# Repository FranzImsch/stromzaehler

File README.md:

## Hardware
Features:
- IR interface for a [smart (DE)](https://youtu.be/aqHauk3bNFA) electricity meter,
- binary input for a gas meter (impulse counter),
- high efficiency buck converter for the USB power supply.

The interface is mounted to the electricity meter using a ring magnet (27 x 5 x 16 mm). The magnet is glued into the 3D-printed [plastic part](https://github.com/FranzImsch/stromzaehler/blob/main/plastic_mount.step) as shown in the picture below.

A [threaded insert (M2)](https://www.digikey.de/en/products/detail/tri-star-industries-inc/M20X157C/13535373) is melted into the plastic piece so that the PCB can be mounted using an M2x5 screw.

Detailed overview: https://a360.co/3Tq192N

Some electricity meters send data without 'request' and therefore the IR-LED along with its circuitry can be omitted in those cases. The [Volkszähler (DE)](https://wiki.volkszaehler.org/hardware/channels/meters) site is pretty useful to find information about different meters.

## Software
For Tasmota to use the SML feature, the following must be added to the ```user_config_override.h```-File (as per [documentation](https://tasmota.github.io/docs/Smart-Meter-Interface/)):

```
#ifndef USE_SCRIPT
#define USE_SCRIPT
#endif
#ifndef USE_SML_M
#define USE_SML_M
#endif
#ifdef USE_RULES
#undef USE_RULES
#endif
```
The software is compiled using the 8M tasmota32 preset. Flashed using [this](https://github.com/FranzImsch/CP2104-M8) serial adapter.

As soon as the device is connected to WiFi, the script for the electricity meter can be entered into the console (as per [documentation](https://tasmota.github.io/docs/Smart-Meter-Interface/#iskra-mt-681-sml)). The RX (25) and TX (26) GPIOs have to be adjusted. The script might need to be adjusted for the very meter that is used. For that, [this](https://tasmota-sml-parser.azurewebsites.net/) tool was tremendously helpful.

The **gas meter** is read with a reed contact. IO27 is set as a counter in Tasmota. What 1 Tick corresponds to in terms of gas is usually written somewhere on the meter. The counter is debounced using the [```CounterDebounce 250```](https://tasmota.github.io/docs/Commands/#sensors) command (which corresponds to 250 ms debounce time).

Also, the TelePeriod was set to 10 seconds (the fastest) as per [documentation](https://tasmota.github.io/docs/Commands/#mqtt).

## Links
- [3D model](https://a360.co/3Tq192N)  
- [Schematic](https://franz.science/stromzaehler/KiCad-Files/Schematic.pdf)  
- [iBom](https://franz.science/stromzaehler/ibom/)  
- [Tasmota](https://github.com/arendst/tasmota)

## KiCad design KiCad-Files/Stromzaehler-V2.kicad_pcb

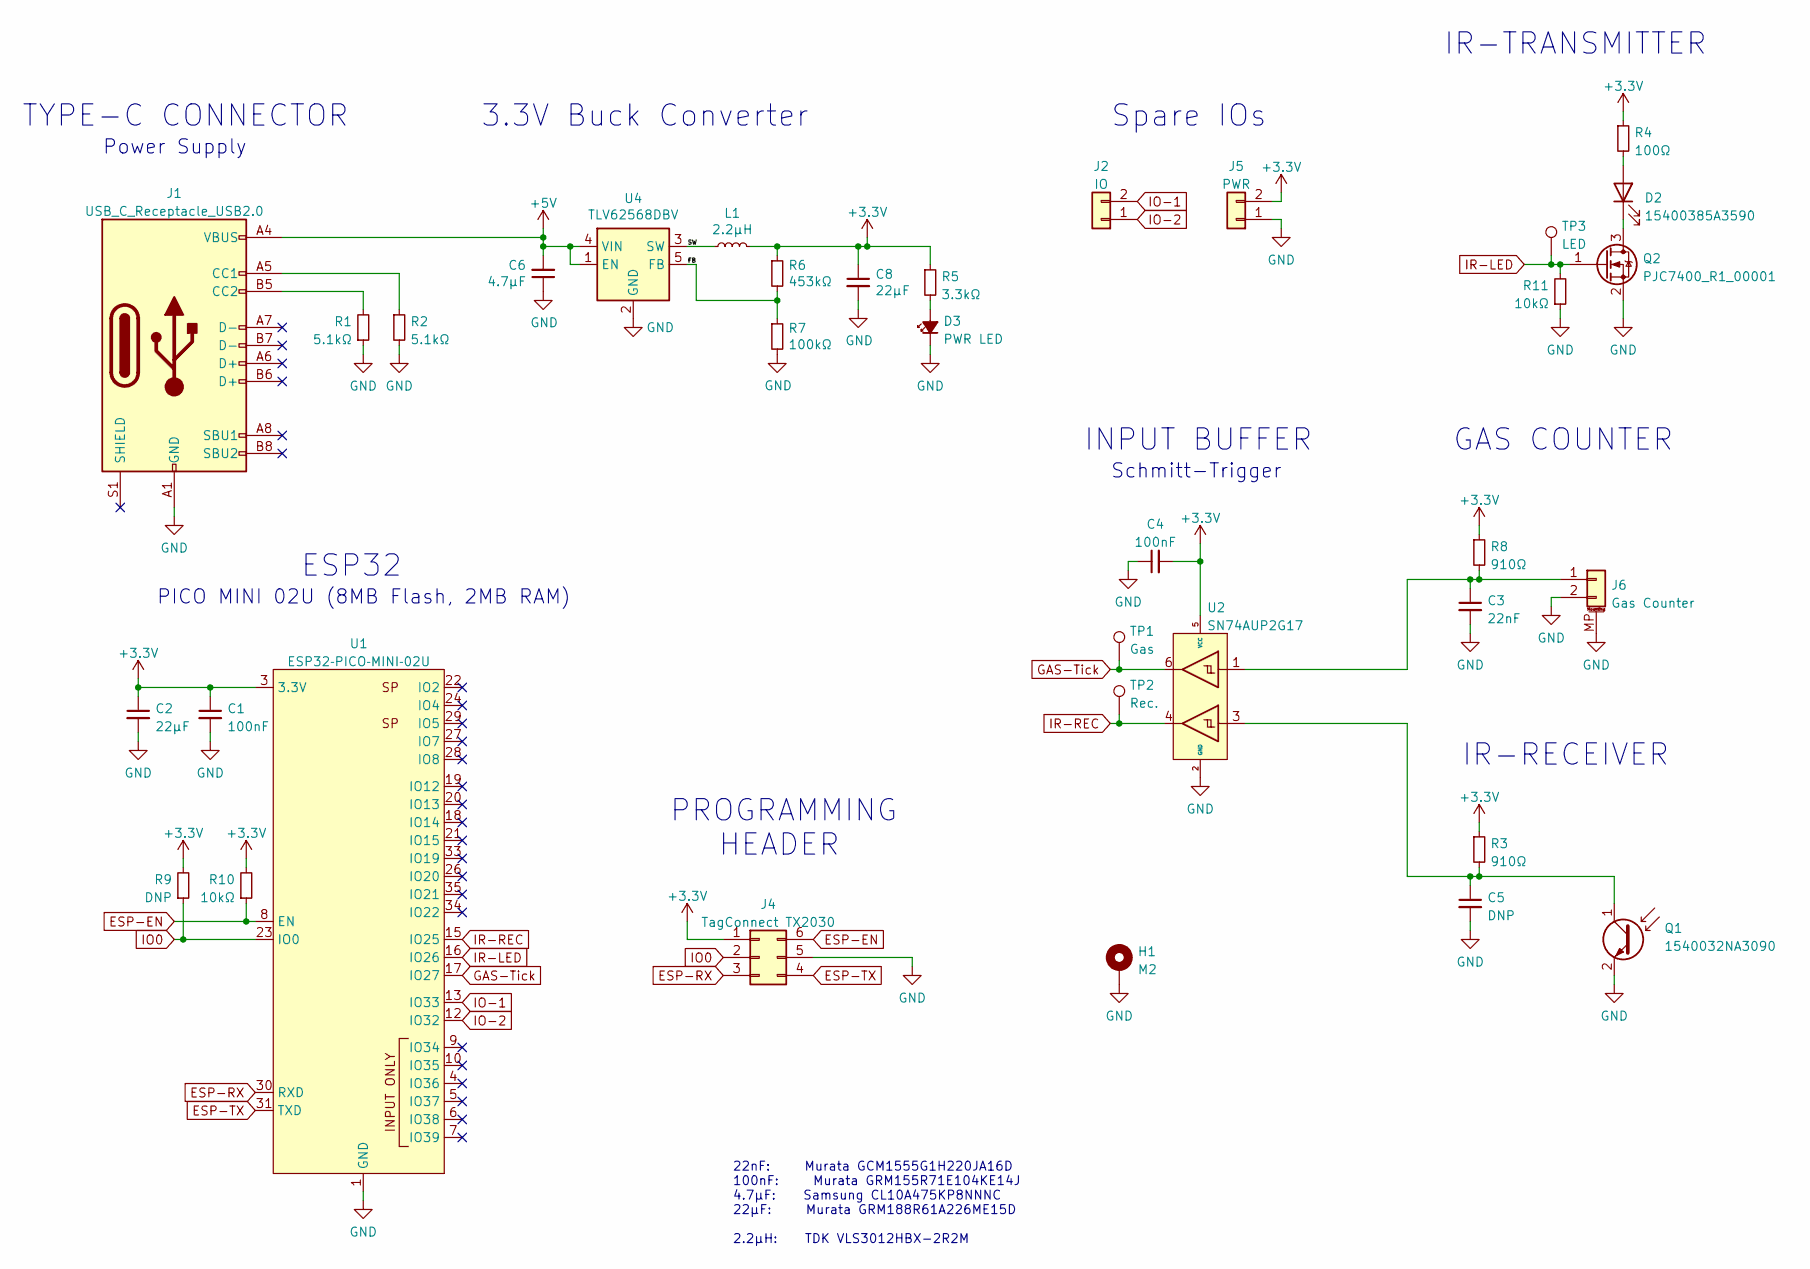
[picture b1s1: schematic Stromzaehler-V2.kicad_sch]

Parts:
C1, C4: 100nF; C_0402_1005Metric_NoSilk
C2, C8: 22µF; C_0603_1608Metric_NoSilk
C3: 22nF; C_0402_1005Metric_NoSilk
C5: DNP; C_0402_1005Metric_NoSilk_DNP
C6: 4.7µF; C_0603_1608Metric_NoSilk
D2: 15400385A3590; LED_D3.0mm_IRBlack_NoSillk
D3: PWR LED; LED_0603_1608Metric_SmallSilk
H1: M2; MountingHole_2.2mm_M2_Pad_Via_NoSilk
J1: USB_C_Receptacle_USB2.0; USB_C_Receptacle_C313131_TYPE-C-31-M-12
J2: IO; PinHeader_1x02_P2.54mm_Vertical_NoSilk
J4: TagConnect TX2030; Tag-Connect_TC2030-IDC-NL_2x03_P1.27mm_Vertical_NoSilk
J5: PWR; PinHeader_1x02_P2.54mm_Vertical_NoSilk
J6: Gas Counter; JST_SH_SM02B-SRSS-TB_1x02-1MP_P1.00mm_Horizontal_NoSilk
L1: 2.2µH; L_Wuerth_MAPI-3012_NoSilk
Q1: 1540032NA3090; LED_D3.0mm_IRBlack_NoSillk
Q2: PJC7400_R1_00001; SOT-323_SC-70_NoSilk
R1, R2: 5.1kΩ; R_0402_1005Metric_NoSilk
R3, R8: 910Ω; R_0402_1005Metric_NoSilk
R4: 100Ω; R_0603_1608Metric_NoSilk
R5: 3.3kΩ; R_0402_1005Metric_NoSilk
R6: 453kΩ; R_0603_1608Metric_NoSilk
R7: 100kΩ; R_0603_1608Metric_NoSilk
R9: DNP; R_0402_1005Metric_NoSilk_DNP
R10, R11: 10kΩ; R_0402_1005Metric_NoSilk
TP1: Gas; TestPoint_Pad_D1.0mm_NoSIlk
TP2: Rec.; TestPoint_Pad_D1.0mm_NoSIlk
TP3: LED; TestPoint_Pad_D1.0mm_NoSIlk
U1: ESP32­PICO­MINI­02U; ESP32-PICO-MINI-02U
U2: SN74AUP2G17; SOT-363_SC-70-6_NoSilk
U4: TLV62568DBV; SOT-23-5_NoSilk

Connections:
+3.3V: C1.1, C2.1, C4.2, C8.1, J4.1, J5.2, L1.2, R3.1, R4.1, R5.1, R6.1, R8.1, R9.2, R10.2, U1.3 (3.3V), U2.5 (VCC)
+5V: C6.2, J1.A4 (VBUS), J1.A9 (VBUS), J1.B4 (VBUS), J1.B9 (VBUS), U4.1 (EN), U4.4 (VIN)
/FB: R6.2, R7.1, U4.5 (FB)
/SW: L1.1, U4.3 (SW)
ESP-EN: J4.6, R10.1, U1.8 (EN)
ESP-RX: J4.3, U1.30 (RXD)
ESP-TX: J4.4, U1.31 (TXD)
GAS-Tick: TP1.1, U1.17 (IO27), U2.6
GND: C1.2, C2.2, C3.2, C4.1, C5.2, C6.1, C8.2, D3.1 (K), H1.1, J1.A1 (GND), J1.A12 (GND), J1.B1 (GND), J1.B12 (GND), J4.5, J5.1, J6.2, J6.MP (MountPin), Q1.2 (E), Q2.2 (S), R1.1, R2.2, R7.2, R11.1, U1.1 (GND), U1.2 (GND), U1.11 (GND), U1.14 (GND), U1.49 (GND), U2.2 (GND), U4.2 (GND)
IO0: J4.2, R9.1, U1.23 (IO0)
IO-1: J2.2, U1.13 (IO33)
IO-2: J2.1, U1.12 (IO32)
IR-LED: Q2.1 (G), R11.2, TP3.1, U1.16 (IO26)
IR-REC: TP2.1, U1.15 (IO25), U2.4
unnamed: C3.1, J6.1, R8.2, U2.1
unnamed: C5.1, Q1.1 (C), R3.2, U2.3
unnamed: D2.1 (K), Q2.3 (D)
unnamed: D2.2 (A), R4.2
unnamed: D3.2 (A), R5.2
unnamed: J1.A5 (CC1), R2.1
unnamed: J1.B5 (CC2), R1.2

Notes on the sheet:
INPUT BUFFER
Spare IOs
GAS COUNTER
22nF: Murata GCM1555G1H220JA16D 100nF: Murata GRM155R71E104KE14J 4.7µF: Samsung CL10A475KP8NNNC 22µF: Murata GRM188R61A226ME15D 2.2µH: TDK VLS3012HBX-2R2M
Schmitt-Trigger
PICO MINI 02U (8MB Flash, 2MB RAM)
3.3V Buck Converter
TYPE-C CONNECTOR
Power Supply
ESP32
PROGRAMMING HEADER
IR-RECEIVER
IR-TRANSMITTER

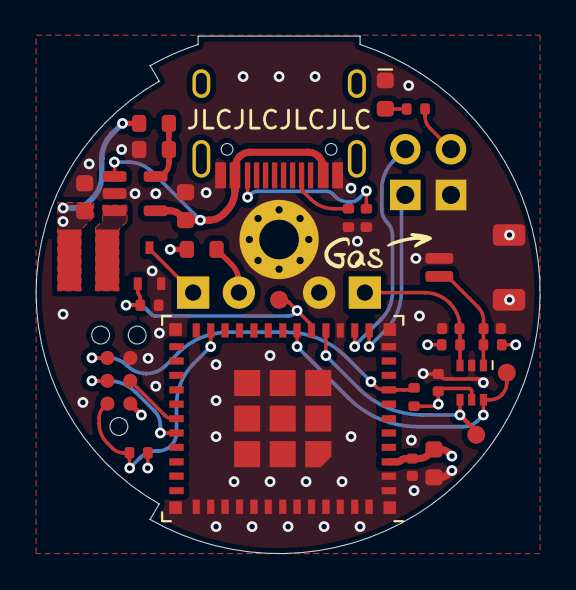
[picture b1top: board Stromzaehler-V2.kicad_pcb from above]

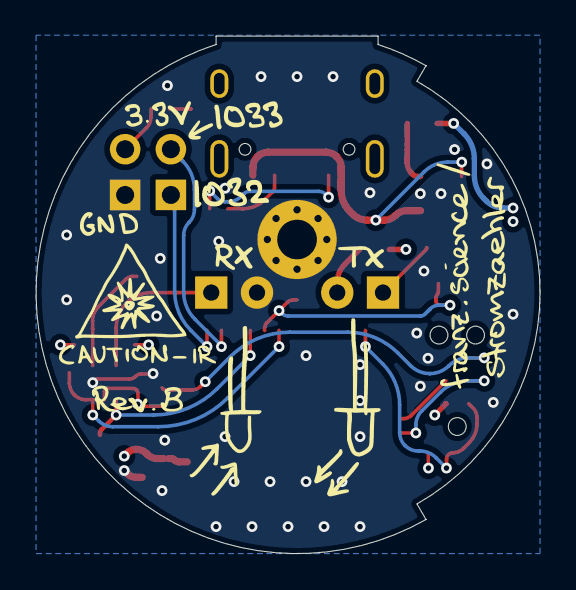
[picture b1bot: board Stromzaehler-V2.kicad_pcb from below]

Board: 4 copper layers, 28.0 x 28.7 mm, 35 parts (2 on the bottom side), 21 nets.

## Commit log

2022-11-07 init repo with README
2022-11-07 added kicad files
2022-11-07 fixed README
2022-11-07 added redirect
2022-11-16 finished testing device
2022-11-20 enhanced readme
2022-11-20 added cross section photo to readme
